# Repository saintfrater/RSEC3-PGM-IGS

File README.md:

# RSEC3-PGM-IGS
re-do of custom/hybrid component from PGM-IGS 

On an PGM-IGS board, there are some "custom" hybrid IC's called RSEC3.

Those ICs are somehow fragile and are not available on the market.

gc8tech (http://www.igspgm.com/) has reverse engineer the IC's schematics and kindly share it with the community.

## Schematics

Since no PCB has been draw for this, here is my attempt to fill this gape.

## Version 1

## Version 2
Depending of the space you have to fit the replacement, you can turn front/back the angled Row Header:

## BOM
| Reference | Value | Footprint | Q |
| --------- | ----- | --------- | - |
| R1-R4  | 100R | Resistor_SMD R_0603_1608Metric | 4 |
| R5-R8  | 10K  | Resistor_SMD R_0603_1608Metric | 4 |
| RSEC1  |      | 2.54mm pitch Angle Row Header Connector | 1 |

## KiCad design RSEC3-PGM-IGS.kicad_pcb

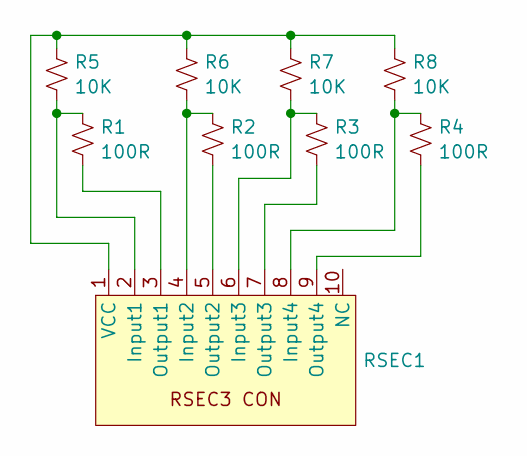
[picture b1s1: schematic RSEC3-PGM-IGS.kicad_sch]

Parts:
R1, R2, R3, R4: 100R; R_0603_1608Metric_Pad0.98x0.95mm_HandSolder
R5, R6, R7, R8: 10K; R_0603_1608Metric_Pad0.98x0.95mm_HandSolder
RSEC1: RSEC3_PCB_Custom

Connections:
unnamed: R1.1, R5.2, RSEC1.2 (Input1)
unnamed: R2.1, R6.2, RSEC1.4 (Input2)
unnamed: R3.1, R7.2, RSEC1.6 (Input3)
unnamed: R4.1, R8.2, RSEC1.8 (Input4)
unnamed: R1.2, RSEC1.3 (Output1)
unnamed: R2.2, RSEC1.5 (Output2)
unnamed: R3.2, RSEC1.7 (Output3)
unnamed: R4.2, RSEC1.9 (Output4)
unnamed: R5.1, R6.1, R7.1, R8.1, RSEC1.1 (VCC)

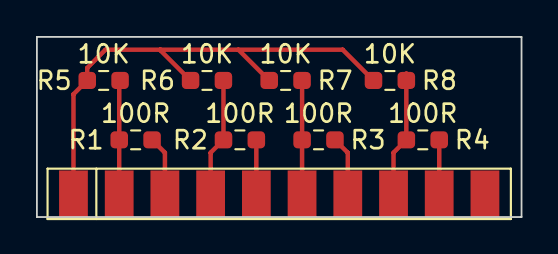
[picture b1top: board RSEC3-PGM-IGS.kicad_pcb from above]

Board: 2 copper layers, 26.9 x 10.0 mm, 9 parts (0 on the bottom side), 9 nets.

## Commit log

2023-08-06 Version 1.00
2023-08-08 Version 2
2023-08-08 Update README.md
    Add Images
2023-08-09 V2-Variant
2023-08-09 Front - Back row variants
